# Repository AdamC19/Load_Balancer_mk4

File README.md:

# Load Balancer mk4
Hardware files for what should be called the Source Balancer.

Don't build this unless you know the risks you are taking. I make no guarantees about the safety, reliablity, or even functionality of the circuit.

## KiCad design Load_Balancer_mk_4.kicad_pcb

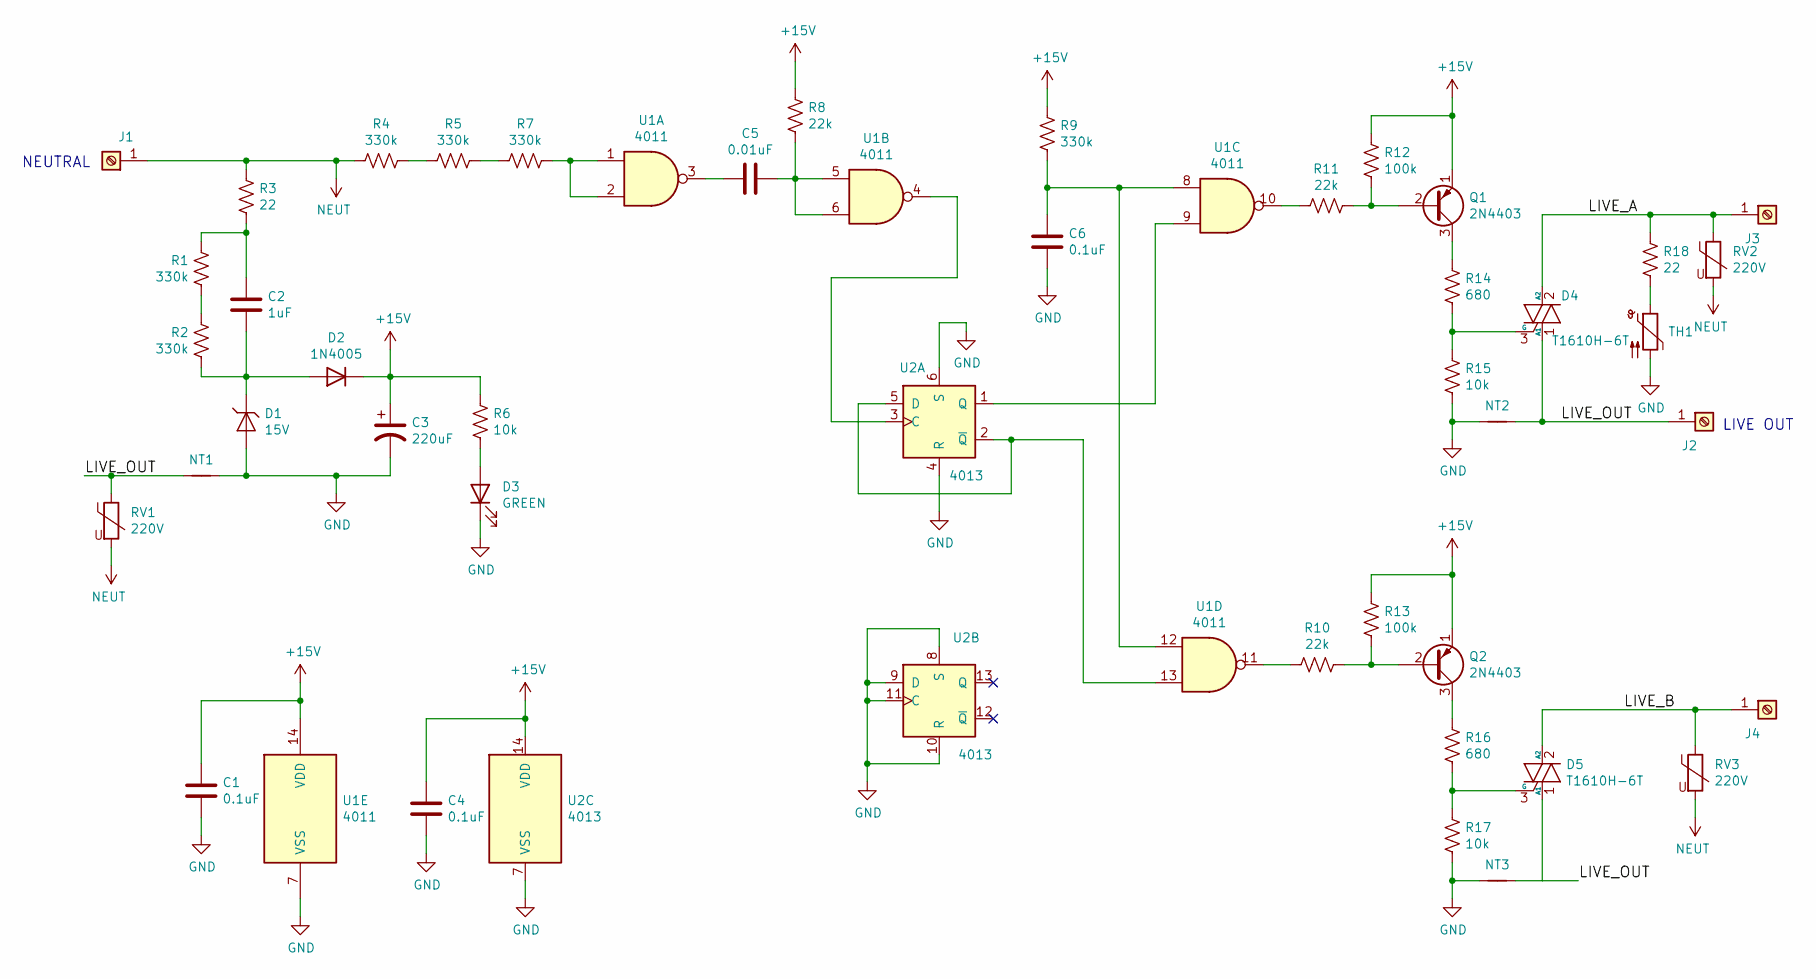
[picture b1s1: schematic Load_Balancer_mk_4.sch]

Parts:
C1, C4, C6: 0.1uF; C_Disc_D5.0mm_W2.5mm_P2.50mm
C2: 1uF; C_Rect_L26.5mm_W8.5mm_P22.50mm_MKS4; MFG_PN R46KN410000P1M
C3: 220uF; CP_Radial_D10.0mm_P5.00mm; MFG_PN 50YXF220MEFC10X16
C5: 0.01uF; C_Disc_D5.0mm_W2.5mm_P2.50mm
D1: 15V; D_DO-41_SOD81_P7.62mm_Horizontal
D2: 1N4005; D_DO-41_SOD81_P10.16mm_Horizontal
D3: GREEN; LED_D5.0mm
D4, D5: T1610H-6T; TO-220-3_Vertical; MFG_PN T1610H-6T
J1, J2, J3, J4: Screw_Terminal_01x01; MountingHole_5.3mm_M5_Pad_Via
NT1, NT2, NT3: Net-Tie_2; NetTie-2_SMD_Pad0.5mm
Q1, Q2: 2N4403; TO-92_Inline_Wide
R1, R2, R4, R5, R7, R9: 330k; R_Axial_DIN0207_L6.3mm_D2.5mm_P10.16mm_Horizontal
R3, R18: 22; R_Axial_DIN0414_L11.9mm_D4.5mm_P15.24mm_Horizontal
R6, R15, R17: 10k; R_Axial_DIN0207_L6.3mm_D2.5mm_P10.16mm_Horizontal
R8, R10, R11: 22k; R_Axial_DIN0207_L6.3mm_D2.5mm_P10.16mm_Horizontal
R12, R13: 100k; R_Axial_DIN0207_L6.3mm_D2.5mm_P10.16mm_Horizontal
R14, R16: 680; R_Axial_DIN0207_L6.3mm_D2.5mm_P10.16mm_Horizontal
RV1, RV2, RV3: 220V; RV_Disc_D12mm_W4.2mm_P7.5mm
TH1: Thermistor_PTC; RV_Disc_D9mm_W3.8mm_P5mm; MFG_PN LVR016K-2
U1: 4011; DIP-14_W7.62mm
U2: 4013; DIP-14_W7.62mm

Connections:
+15V: C1.1, C3.1, C4.1, D2.1 (K), Q1.1 (E), Q2.1 (E), R6.1, R8.2, R9.2, R12.1, R13.1, U1.14 (VDD), U2.14 (VDD)
/LIVE_A: D4.2 (A2), J3.1, R18.1, RV2.1
/LIVE_B: D5.2 (A2), J4.1, RV3.1
/LIVE_OUT: D4.1 (A1), D5.1 (A1), J2.1, NT1.1, NT2.2, NT3.2, RV1.1
GND: C1.2, C3.2, C4.2, C6.2, D1.2 (A), D3.1 (K), NT1.2, NT2.1, NT3.1, R15.2, R17.2, TH1.2, U1.7 (VSS), U2.4 (R), U2.6 (S), U2.7 (VSS), U2.8 (S), U2.9 (D), U2.10 (R), U2.11 (C)
NEUT: J1.1, R3.1, R4.1, RV1.2, RV2.2, RV3.2
unnamed: C2.1, R1.2, R3.2
unnamed: C2.2, D1.1 (K), D2.2 (A), R2.1
unnamed: C5.1, U1.3
unnamed: C5.2, R8.1, U1.5, U1.6
unnamed: C6.1, R9.1, U1.8, U1.12
unnamed: D3.2 (A), R6.2
unnamed: D4.3 (G), R14.2, R15.1
unnamed: D5.3 (G), R16.2, R17.1
unnamed: Q1.2 (B), R11.2, R12.2
unnamed: Q1.3 (C), R14.1
unnamed: Q2.2 (B), R10.2, R13.2
unnamed: Q2.3 (C), R16.1
unnamed: R1.1, R2.2
unnamed: R4.2, R5.1
unnamed: R5.2, R7.1
unnamed: R7.2, U1.1, U1.2
unnamed: R10.1, U1.11
unnamed: R11.1, U1.10
unnamed: R18.2, TH1.1
unnamed: U1.4, U2.3 (C)
unnamed: U1.9, U2.1 (Q)
unnamed: U1.13, U2.2 (~Q), U2.5 (D)

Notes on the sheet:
NEUTRAL
LIVE OUT

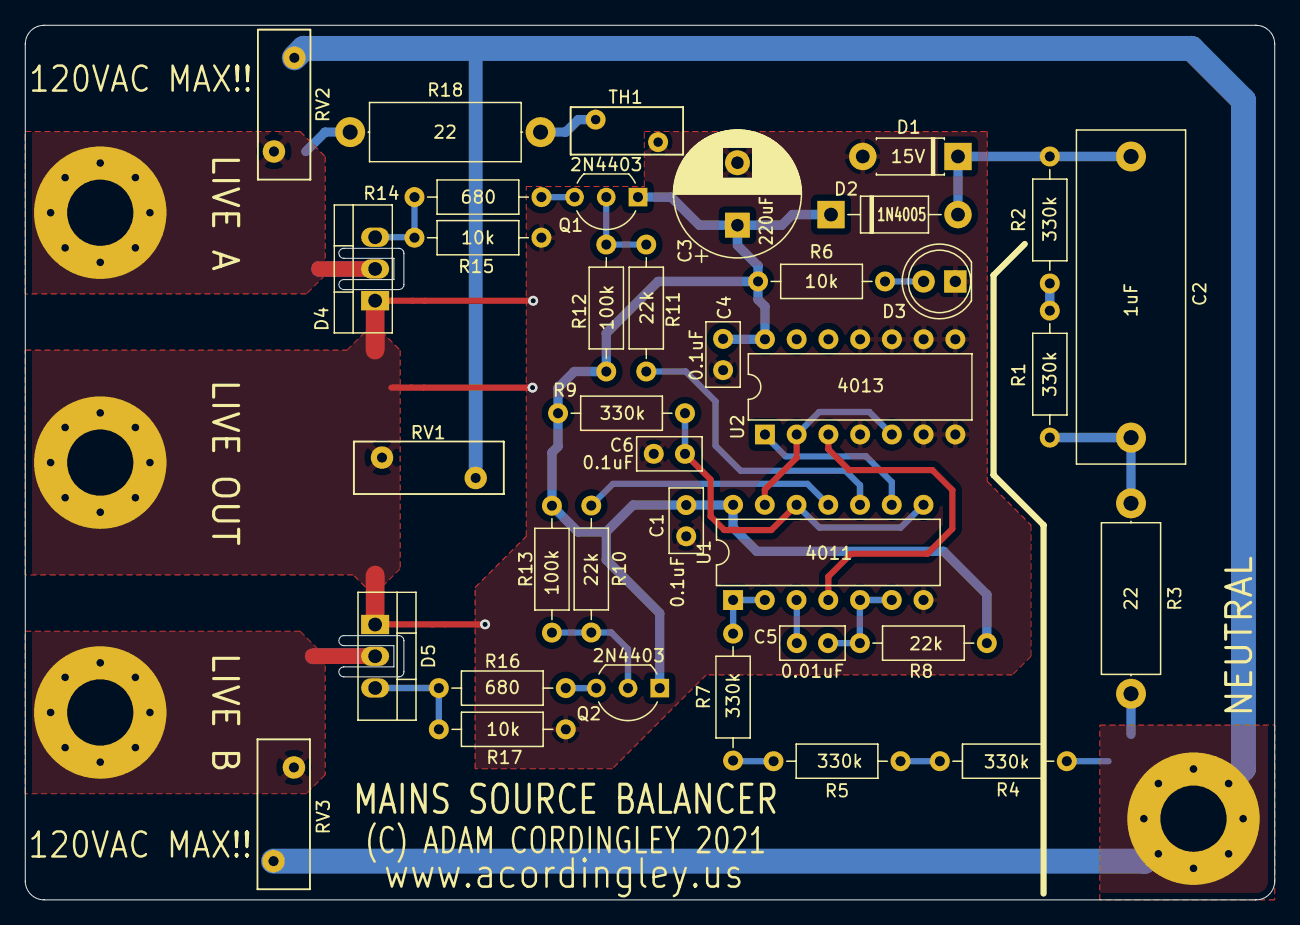
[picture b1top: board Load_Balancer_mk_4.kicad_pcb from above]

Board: 2 copper layers, 100.0 x 70.0 mm, 44 parts (0 on the bottom side), 28 nets.

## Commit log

2021-12-11 Add gitignore
2021-12-11 Add some silkscreen text
2021-12-11 Add gerbers
